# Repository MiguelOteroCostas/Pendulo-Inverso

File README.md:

# Pendulo-Inverso
En este txt iré describiendo alguno de los pasos y procesos que iré siguiendo con el objetivo de crear un pendulo inverso.
PLANNING:
1. Buscar referencias
2. Encontrar huellas de los elementos requeridos
3. Montar las huellas que sean necesarias
4. Juntarlas todas en una sola PCB
5. Llevarla a Enrique para comprobar que funciona correctamente, y si no es así, corregir los errores
6. Una vez comprobado que la PCB funciona a la perfección, encargar su fabricación por Internet
https://www.pcbway.es/?currency=3
7. Conseguir los motores y las ruedas
https://www.amazon.es/Gebildet-Motorreductor-Tracción-Robótico-Neumático/dp/B08D39MFN1/ref=asc_df_B08D39MFN1/?tag=&linkCode=df0&hvadid=420349540689&hvpos=&hvnetw=g&hvrand=10269854428416406848&hvpone=&hvptwo=&hvqmt=&hvdev=c&hvdvcmdl=&hvlocint=&hvlocphy=1005480&hvtargid=pla-937905506568&mcid=4c17839e2fe332fd8fbfa763e271e5d1&ref=&adgrpid=94419898965&th=1
8. Diseñar una carcasa en 3D e imprimirla en la politécnica
9. Montar y soldar todo
10. Comprobar su funcionamiento y que cumple los requisitos pedidos en la práctica
11. Pulir detalles

1
2
3 Conexion ESP32 con MPU 6050: https://www.youtube.com/watch?v=iLVahH4MrwQ

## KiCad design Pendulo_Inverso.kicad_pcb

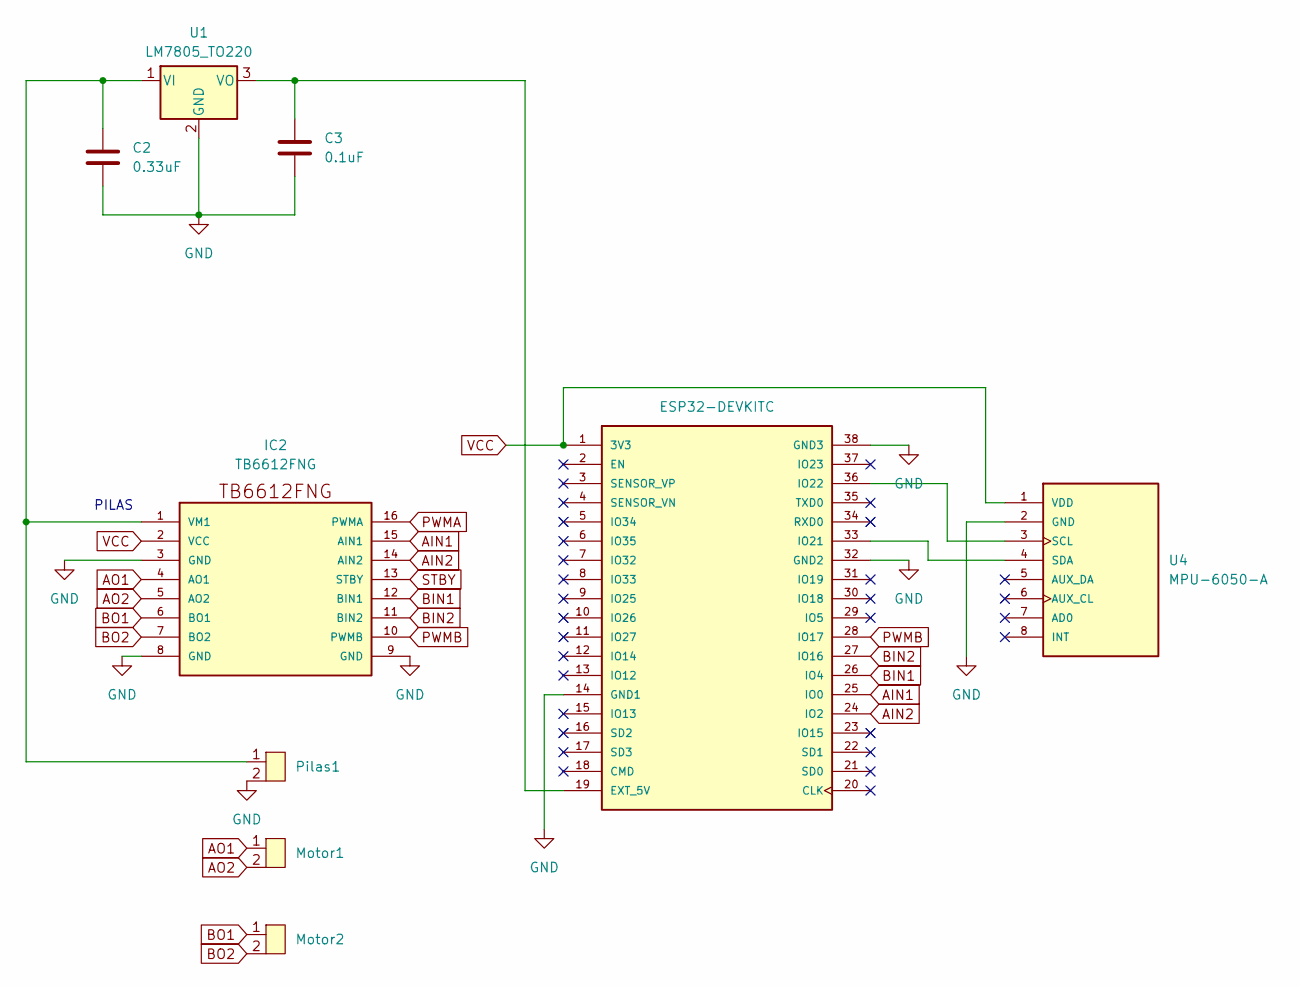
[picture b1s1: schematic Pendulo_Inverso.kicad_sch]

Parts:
C2: 0.33uF; CP_Radial_D8.0mm_P3.50mm
C3: 0.1uF; CP_Radial_D8.0mm_P3.50mm
IC2: TB6612FNG; TB6612FngSparkfun
Motor1, Motor2: TerminalBlock_Phoenix_MKDS-1,5-2_1x02_P5.00mm_Horizontal
Pilas1: TerminalBlock_Phoenix_MKDS-1,5-2_1x02_P5.00mm_Horizontal
U1: LM7805_TO220; TO-220-3_Vertical
U2: ESP32-DEVKITC; MODULE_ESP32-DEVKITC; PARTREV N/A
U4: MPU-6050-A; MPU6050; PARTREV 3.4

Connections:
AIN1: IC2.15 (AIN1), U2.25 (IO0)
AIN2: IC2.14 (AIN2), U2.24 (IO2)
AO1: IC2.4 (AO1), Motor1.1
AO2: IC2.5 (AO2), Motor1.2
BIN1: IC2.12 (BIN1), U2.26 (IO4)
BIN2: IC2.11 (BIN2), U2.27 (IO16)
BO1: IC2.6 (BO1), Motor2.1
BO2: IC2.7 (BO2), Motor2.2
GND: C2.2, C3.2, IC2.3 (GND), IC2.8 (GND), IC2.9 (GND), Pilas1.2, U1.2 (GND), U2.14 (GND1), U2.32 (GND2), U2.38 (GND3), U4.2 (GND)
unnamed: C2.1, IC2.1 (VM1), Pilas1.1, U1.1 (VI)
unnamed: C3.1, U1.3 (VO), U2.19 (EXT_5V)
unnamed: U2.33 (IO21), U4.4 (SDA)
unnamed: U2.36 (IO22), U4.3 (SCL)
PWMA: IC2.16 (PWMA)
PWMB: IC2.10 (PWMB), U2.28 (IO17)
STBY: IC2.13 (STBY)
VCC: IC2.2 (VCC), U2.1 (3V3), U4.1 (VDD)

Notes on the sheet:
PILAS

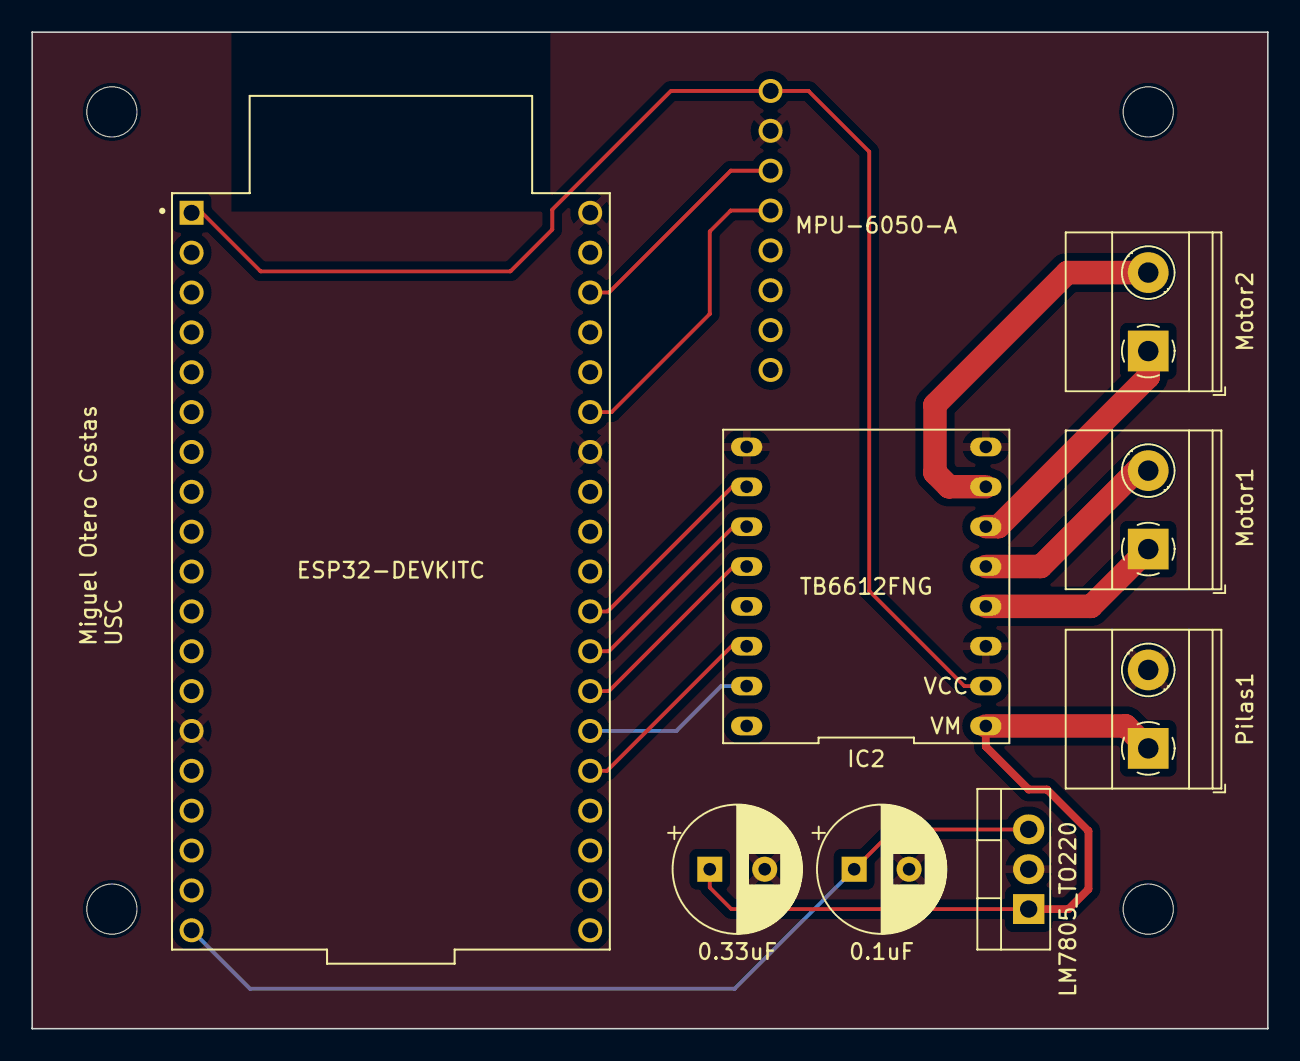
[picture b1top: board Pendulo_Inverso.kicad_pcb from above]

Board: 2 copper layers, 78.7 x 63.5 mm, 9 parts (0 on the bottom side), 15 nets.

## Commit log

2024-03-16 README.md
2024-03-16 prototipo.cpp
2024-03-28 new file: Pendulo_Inverso-backups/Pendulo_Inverso-2024-03-22_111232.zip new file: Pendulo_Inverso-backups/Pendulo_Inverso-2024-03-22_111732.zip new file: Pendulo_Inverso-backups/Pendulo_Inverso-2024-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
2024-03-29 modified: Pendulo_Inverso.dsn modified: Pendulo_Inverso.kicad_pcb modified: Pendulo_Inverso.kicad_prl modified: Pendulo_Inverso.kicad_sch modified: Pendulo_Inverso.rules modified: Pendulo_Inverso.ses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
2024-04-04 new file: Pendulo_Inverso-backups/Pendulo_Inverso-2024-04-04_134628.zip modified: Pendulo_Inverso.kicad_pcb modified: Pendulo_Inverso.kicad_prl modified: Pendulo_Inverso.kicad_pro modified: Pendulo_I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
2024-04-04 deleted: Pendulo_Inverso-backups/Pendulo_Inverso-2024-04-04_113047.zip deleted: Pendulo_Inverso-backups/Pendulo_Inverso-2024-04-04_130756.zip deleted: Pendulo_Inverso-backups/Pendulo_Inverso-2024-04-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
2024-04-11 deleted: Pendulo_Inverso-backups/Pendulo_Inverso-2024-04-04_183334.zip deleted: Pendulo_Inverso-backups/Pendulo_Inverso-2024-04-04_183941.zip new file: Pendulo_Inverso-backups/Pendulo_Inverso-2024-04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
2024-04-11 deleted: Pendulo_Inverso-backups/Pendulo_Inverso-2024-03-22_111232.zip new file: Pendulo_Inverso-backups/Pendulo_Inverso-2024-04-06_125540.zip new file: Pendulo_Inverso-backups/Pendulo_Inverso-2024-0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
2024-04-20 deleted: Pendulo_Inverso-backups/Pendulo_Inverso-2024-03-22_111732.zip deleted: Pendulo_Inverso-backups/Pendulo_Inverso-2024-03-22_112740.zip deleted: Pendulo_Inverso-backups/Pendulo_Inverso-2024-03-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
